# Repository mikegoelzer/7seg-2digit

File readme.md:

# Two Digit 7-Segment Display

This repository contains the design files for a 2-digit 7-segment display PMOD, modeled after the Digilent PMOD design but without a dual-row Dupont male header pinout. The display is designed for 3.3V operation and uses multiplexing to control both digits using only 8 GPIOs (7 for segments, one for left/right digit select).

## Features

- 2-digit 7-segment display
- 3.3V operation
- Multiplexed design (8 GPIOs control both digits)

## Schematic

The schematic for this design can be found in the [docs/schematic.pdf](docs/schematic.pdf) file.

## Repository Structure

- `7Seg-Kicad/`: KiCad project files
- `bom/`: Excel sheet with Digikey/Mouser part numbers
- `docs/`: Documentation, including the schematic PDF
- `img/`: Images, including the 3D rendering
- `Parts/`: Parts imported into Kicad project

## Usage

This PCB can be used with any FPGA or microcontroller board, although it uses a non-standard pinout (for PMODs). The multiplexed design allows for efficient control of both digits using minimal GPIO pins.

## License

[GPLv3](https://www.gnu.org/licenses/gpl-3.0.en.html)

## Contributing

We welcome contributions to improve this design. Please feel free to submit issues or pull requests.

## Acknowledgements

This design is inspired by the [Digilent PMOD 7-segment display](https://digilent.com/shop/pmod-ssd-seven-segment-display/) but has been modified to fit a custom board and does not conform to the normal PMOD pinout.

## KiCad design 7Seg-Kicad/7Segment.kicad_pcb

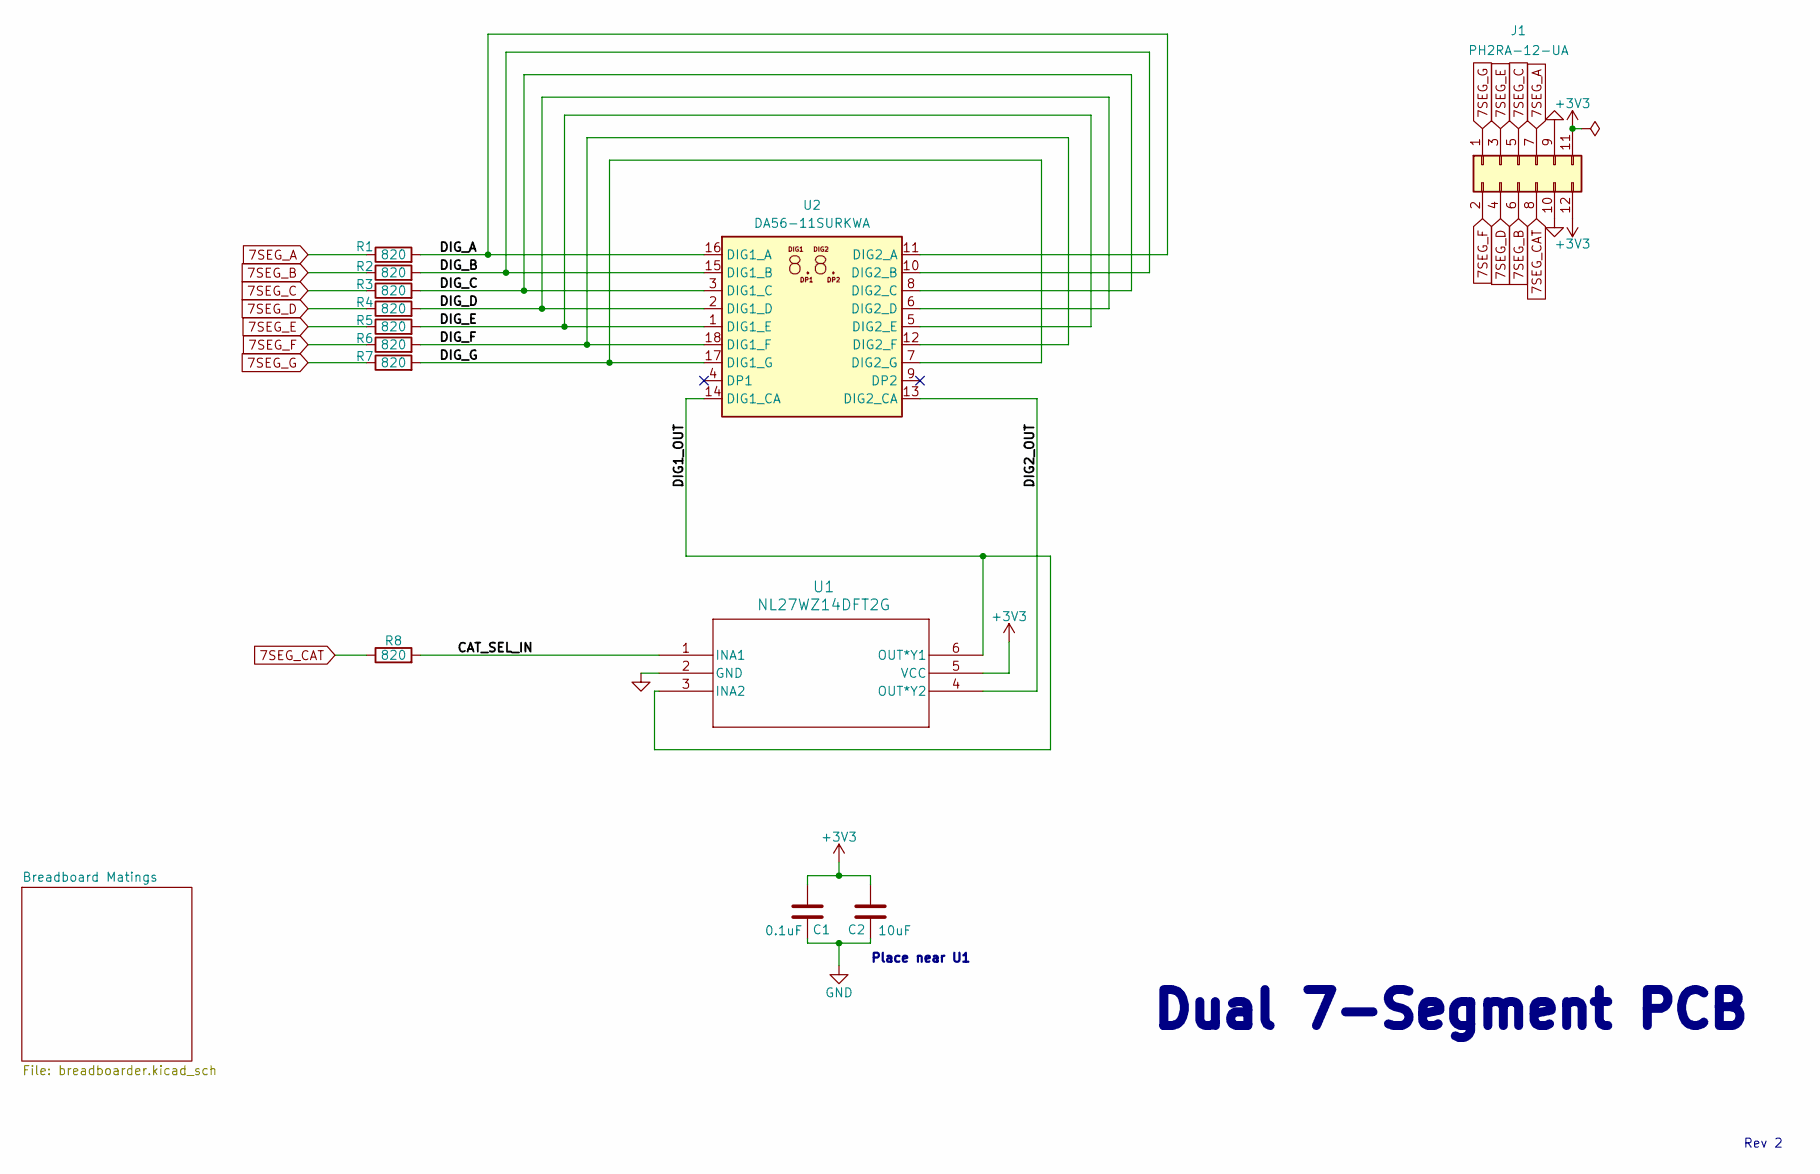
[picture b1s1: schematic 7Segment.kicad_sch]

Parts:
C1: 0.1uF; C_1206_3216Metric_Pad1.33x1.80mm_HandSolder
C2: 10uF; C_1206_3216Metric_Pad1.33x1.80mm_HandSolder
J1: PH2RA-12-UA; PinSocket_2x06_P2.54mm_Vertical; MPN PH2RA-12-UA
R1, R2, R3, R4, R5, R6, R7, R8: 820; R_1206_3216Metric_Pad1.42x1.75mm_HandSolder
U1: NL27WZ14DFT2G; SC70-6_ONS
U2: DA56-11SURKWA

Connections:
7SEG_A: J1.7, R1.1
7SEG_B: J1.6, R2.1
7SEG_C: J1.5, R3.1
7SEG_CAT: J1.8, R8.1
7SEG_D: J1.4, R4.1
7SEG_E: J1.3, R5.1
7SEG_F: J1.2, R6.1
7SEG_G: J1.1, R7.1
+3V3: C1.2, C2.2, J1.11, J1.12, U1.5 (VCC)
/CAT_SEL_IN: R8.2, U1.1 (INA1)
/DIG1_OUT: U1.3 (INA2), U1.6 (OUT*Y1), U2.14 (DIG1_CA)
/DIG2_OUT: U1.4 (OUT*Y2), U2.13 (DIG2_CA)
/DIG_A: R1.2, U2.11 (DIG2_A), U2.16 (DIG1_A)
/DIG_B: R2.2, U2.10 (DIG2_B), U2.15 (DIG1_B)
/DIG_C: R3.2, U2.3 (DIG1_C), U2.8 (DIG2_C)
/DIG_D: R4.2, U2.2 (DIG1_D), U2.6 (DIG2_D)
/DIG_E: R5.2, U2.1 (DIG1_E), U2.5 (DIG2_E)
/DIG_F: R6.2, U2.12 (DIG2_F), U2.18 (DIG1_F)
/DIG_G: R7.2, U2.7 (DIG2_G), U2.17 (DIG1_G)
GND: C1.1, C2.1, J1.9, J1.10, U1.2 (GND)

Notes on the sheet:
Place near U1
Rev 2
Dual 7-Segment PCB

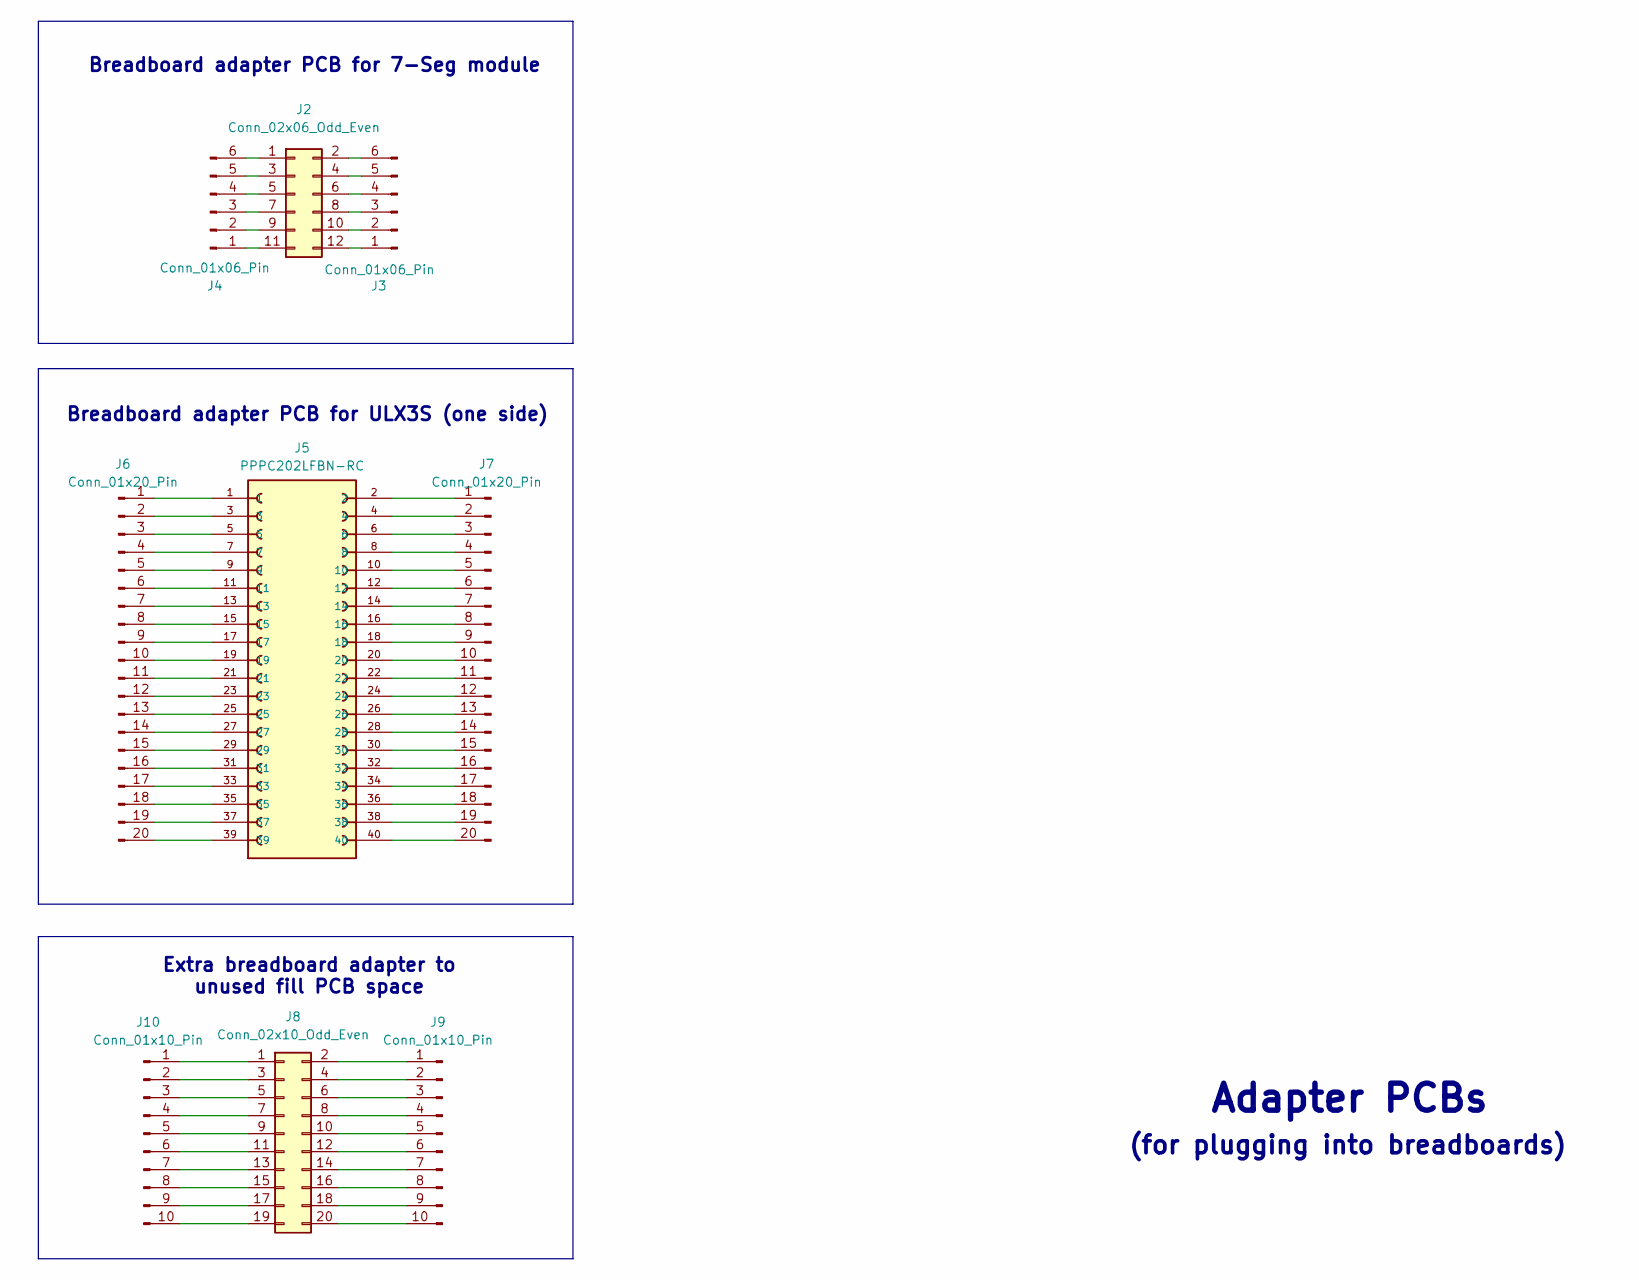
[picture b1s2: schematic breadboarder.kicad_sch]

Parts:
J2: Conn_02x06_Odd_Even; PinSocket_2x06_P2.54mm_Vertical
J3, J4: Conn_01x06_Pin; PinHeader_1x06_P2.54mm_Vertical
J5: PPPC202LFBN-RC; SULLINS_PPPC202LFBN-RC; PARTREV L
J6, J7: Conn_01x20_Pin; PinHeader_1x20_P2.54mm_Vertical
J8: Conn_02x10_Odd_Even; PinSocket_2x10_P2.54mm_Vertical
J9, J10: Conn_01x10_Pin; PinHeader_1x10_P2.54mm_Vertical

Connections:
unnamed: J2.1, J4.6
unnamed: J2.2, J3.6
unnamed: J2.3, J4.5
unnamed: J2.4, J3.5
unnamed: J2.5, J4.4
unnamed: J2.6, J3.4
unnamed: J2.7, J4.3
unnamed: J2.8, J3.3
unnamed: J2.9, J4.2
unnamed: J2.10, J3.2
unnamed: J2.11, J4.1
unnamed: J2.12, J3.1
unnamed: J5.1, J6.1
unnamed: J5.3, J6.2
unnamed: J5.5, J6.3
unnamed: J5.7, J6.4
unnamed: J5.9, J6.5
unnamed: J5.11, J6.6
unnamed: J5.13, J6.7
unnamed: J5.15, J6.8
unnamed: J5.17, J6.9
unnamed: J5.19, J6.10
unnamed: J5.21, J6.11
unnamed: J5.23, J6.12
unnamed: J5.25, J6.13
unnamed: J5.27, J6.14
unnamed: J5.29, J6.15
unnamed: J5.31, J6.16
unnamed: J5.33, J6.17
unnamed: J5.35, J6.18
unnamed: J5.37, J6.19
unnamed: J5.39, J6.20
unnamed: J5.2, J7.1
unnamed: J5.4, J7.2
unnamed: J5.6, J7.3
unnamed: J5.8, J7.4
unnamed: J5.10, J7.5
unnamed: J5.12, J7.6
unnamed: J5.14, J7.7
unnamed: J5.16, J7.8
unnamed: J5.18, J7.9
unnamed: J5.20, J7.10
unnamed: J5.22, J7.11
unnamed: J5.24, J7.12
unnamed: J5.26, J7.13
unnamed: J5.28, J7.14
unnamed: J5.30, J7.15
unnamed: J5.32, J7.16
unnamed: J5.34, J7.17
unnamed: J5.36, J7.18
unnamed: J5.38, J7.19
unnamed: J5.40, J7.20
unnamed: J8.2, J9.1
unnamed: J8.4, J9.2
unnamed: J8.6, J9.3
unnamed: J8.8, J9.4
unnamed: J8.10, J9.5
unnamed: J8.12, J9.6
unnamed: J8.14, J9.7
unnamed: J8.16, J9.8
unnamed: J8.18, J9.9
unnamed: J8.20, J9.10
unnamed: J8.1, J10.1
unnamed: J8.3, J10.2
unnamed: J8.5, J10.3
unnamed: J8.7, J10.4
unnamed: J8.9, J10.5
unnamed: J8.11, J10.6
unnamed: J8.13, J10.7
unnamed: J8.15, J10.8
unnamed: J8.17, J10.9
unnamed: J8.19, J10.10

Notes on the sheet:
(for plugging into breadboards)
Adapter PCBs
Breadboard adapter PCB for 7-Seg module
Breadboard adapter PCB for ULX3S (one side)
Extra breadboard adapter to unused fill PCB space

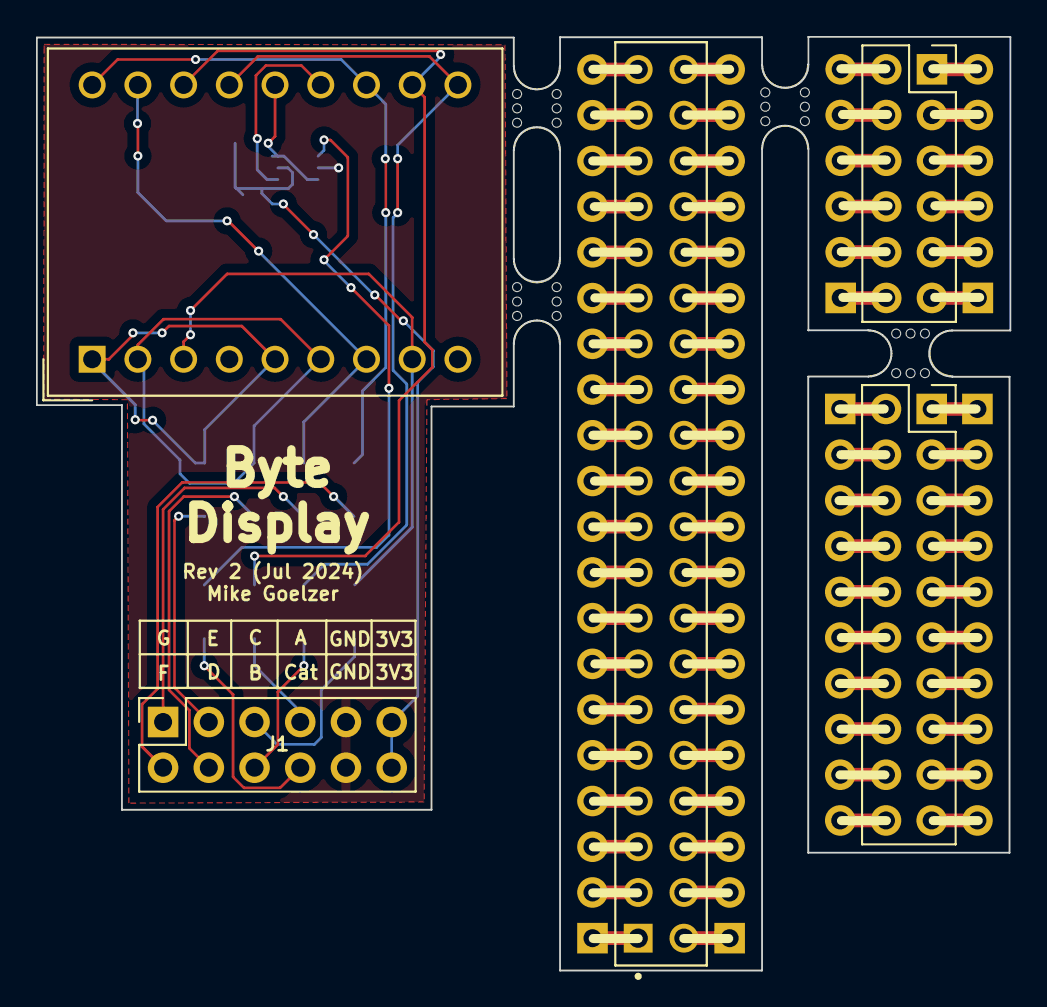
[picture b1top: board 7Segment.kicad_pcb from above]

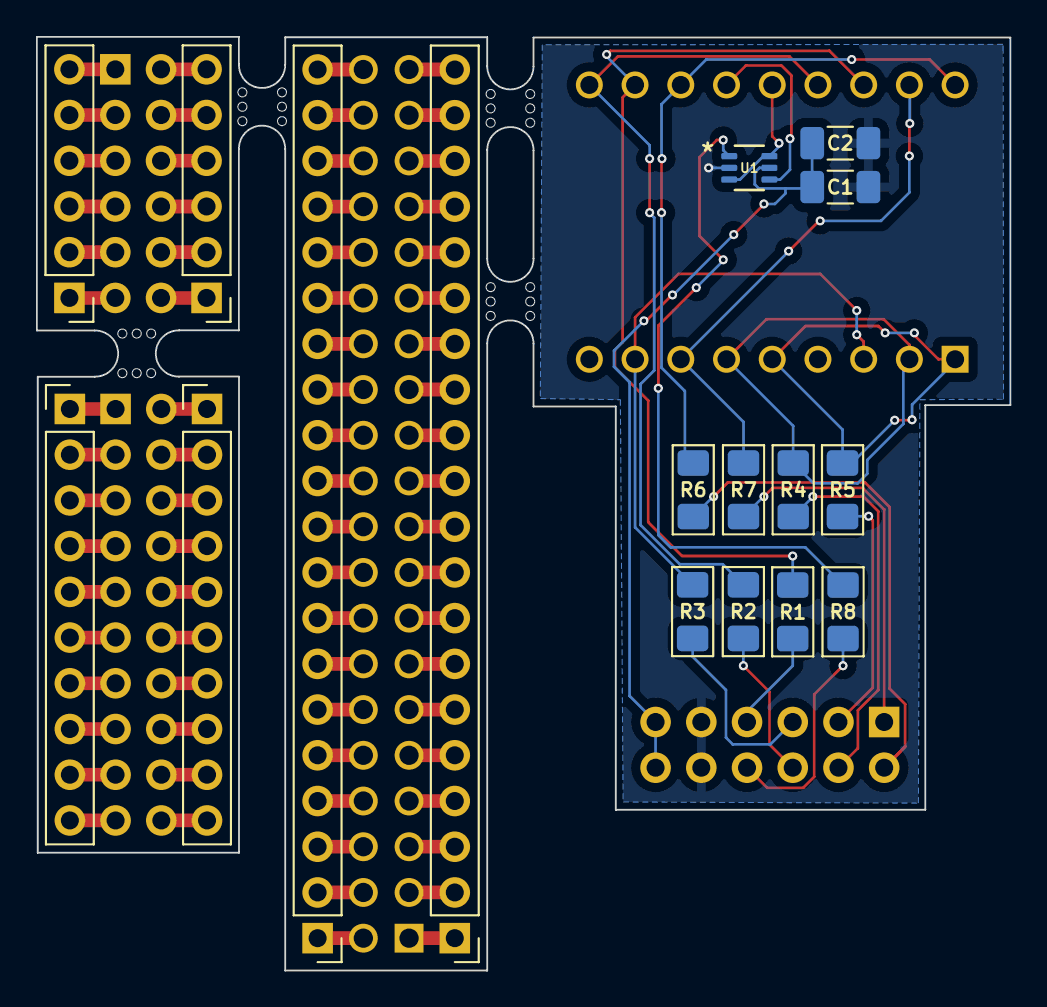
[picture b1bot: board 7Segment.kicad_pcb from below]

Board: 2 copper layers, 54.1 x 51.9 mm, 26 parts (17 on the bottom side), 92 nets.

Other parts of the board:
mouse-bite-2.54mm-slot, mouse-bite-2.54mm-slot#2, mouse-bite-2.54mm-slot#3, mouse-bite-2.54mm-slot#4: VAL**; mouse-bite-2.54mm-slot

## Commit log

2024-08-29 readme update
2024-08-29 revision 0.1
2024-08-30 Revision 2 final
2024-08-30 exclude backup zips from git
2024-08-30 correct part description
2024-08-30 add drill slot to comply with oshpark reqs
